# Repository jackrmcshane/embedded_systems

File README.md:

## Light Sensor System for the Hoosier National Forest

> This repository houses the code, circuit schematics, and 3D models for the light sensor system.

> The light sensor system is an autonomous, ultra-low power embedded microcontroller system designed to take light-level readings from the night sky. Over the course of hte next year, it will be deployed in teh Hoosier National Forest to collect sensor readings for the Forest Service in their attempt to gain 'dark sky' status.

> The software utilized by the system is an interrupt driven program that utilized the system's Real-Time Clock (RTC) to generate regular interrupts at fifteen minute intervals. These intervals are generated between the times of 8:00pm and 8:00am, daily, over the course of the system's one year lifetime so that the sensor system is able to capture how low the light levels reach over the course of each night. These readings are then stored bythe software in the system's FLASH memory back for collection at the end of the device's lifetime.

> TGhe electrical system, responsible for powering the system's CPU and peripheral devices, maximizes its operational life cycle by switching between a high powered running mode used for taking readings and low power mode which conserves the state of the machine whilst still limiting the expense of power. Utilizing the modes of operation that we do, the maximum lifetime of the light sensor system has been estimated to be three years using the STMCube software, allowing confidence that the system can operate for a year without issue.

> As part of the overall system, a 3D printable, water-resistant enclosure has been designed to house the electrical components. An enclosure such as the one we designed is a necessary part of the larger system not only because it will shield the PCB and its components from external forces such as dirt and rain while it is out in the forest, but it will also protect wildlife from damaging the electrical system and vice versa. The enclosure has a securable lid for easy access to the PCB and a port on the bottom of the enclosure for access to a 3-pin connector for later collection of the data captured by the light sensor system.

> The system has been designed to be as low cost as possible such that it may be produced en masse for the Forest Service so that they might deploy the devices throughout the 200,000 acres of the forest and maximize their chances to collect the low-light level readings that they need.

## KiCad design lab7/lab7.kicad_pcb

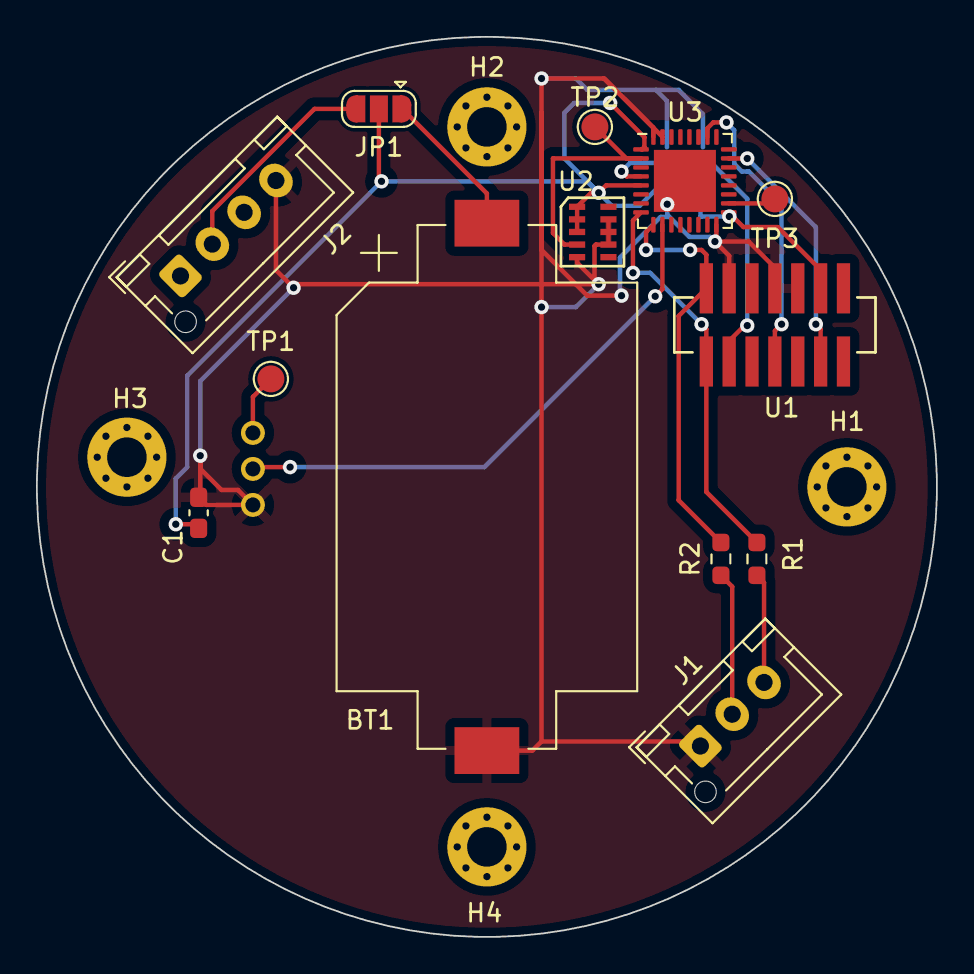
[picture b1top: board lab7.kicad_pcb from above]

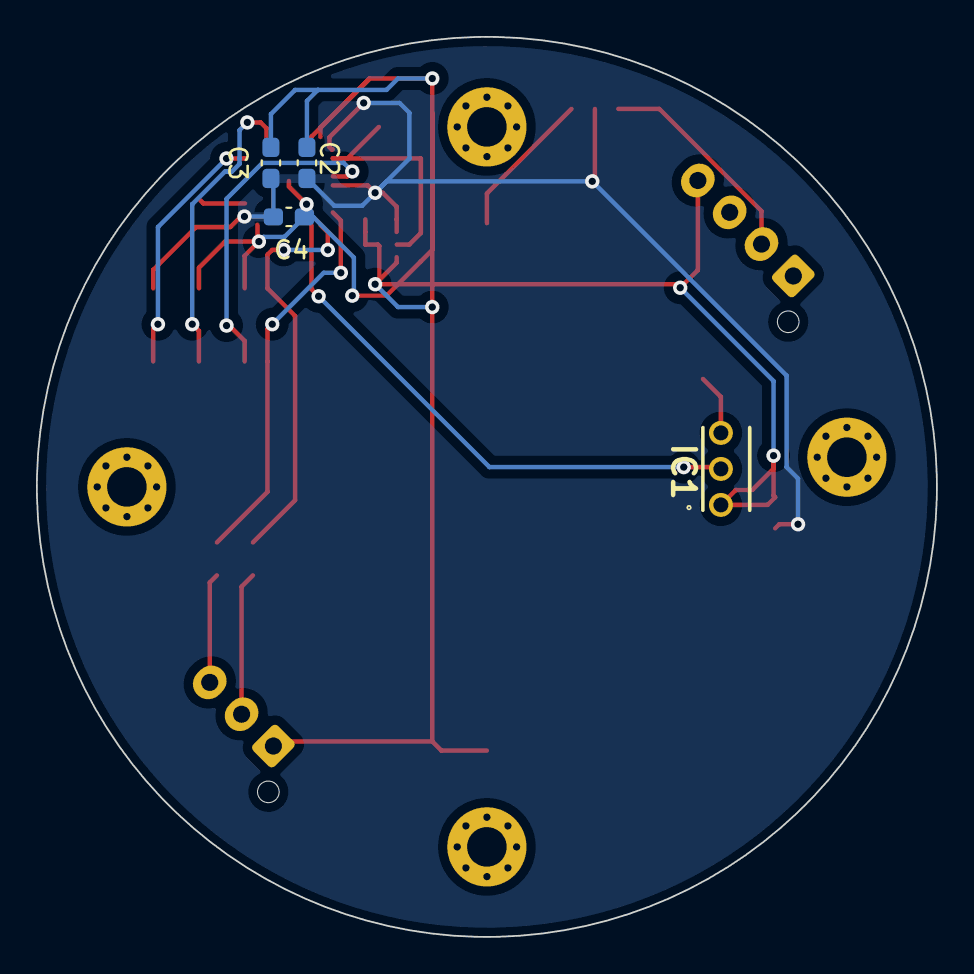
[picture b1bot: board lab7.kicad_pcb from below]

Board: 2 copper layers, 50.0 x 50.0 mm, 21 parts (4 on the bottom side), 15 nets.

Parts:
BT1: Battery_Cell; BatteryHolder_Keystone_1060_1x2032
C1, C3: 1uF; C_0603_1608Metric_Pad1.08x0.95mm_HandSolder
C2, C4: 0.1uF; C_0603_1608Metric_Pad1.08x0.95mm_HandSolder
H1, H2, H3, H4: MountingHole; MountingHole_2.2mm_M2_Pad_Via
IC1: TSL237S-LF
J1: Conn_01x03; JST_XH_B3B-XH-AM_1x03_P2.50mm_Vertical
J2: Conn_01x04; JST_XH_B4B-XH-AM_1x04_P2.50mm_Vertical
JP1: Jumper_3_Open; SolderJumper-3_P1.3mm_Open_RoundedPad1.0x1.5mm
R1, R2: R_US; R_0603_1608Metric_Pad0.98x0.95mm_HandSolder
TP1, TP2, TP3: TestPoint; TestPoint_Pad_D1.5mm
U1: STDC14; ftsh_14p_connector
U2: TG-3541CE
U3: STM32L432KCUx; QFN-32-1EP_5x5mm_P0.5mm_EP3.45x3.45mm

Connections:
/CLKOUT: TP3.1, U3.18 (PA8)
/NRST: U1.12 (NRST), U3.4 (NRST)
/RX: R2.2, U1.13 (VCP_RX), U3.9 (PA3)
/SWDIO: U1.4 (SWDIO), U3.23 (PA13)
/SWO: U1.8 (SWO), U3.26 (PB3)
/TX: R1.2, U1.14 (VCP_TX), U3.8 (PA2)
/oscillator: TP2.1, U2.4 (OUT), U3.2 (PC14)
/sensor_pwr: IC1.2 (VDD), U3.10 (PA4)
GND: BT1.2 (-), C1.2, C2.2, C3.2, C4.2, IC1.1 (GND), J1.1, J2.4, U1.5 (GND), U1.7 (GND), U1.11 (GNDDetect), U2.5 (GND), U2.7 (GND), U2.8 (GND), U2.9 (GND), U3.16 (VSS), U3.31 (PH3), U3.32 (VSS), U3.33 (VSS)
unnamed: BT1.1 (+), JP1.1 (A)
unnamed: IC1.3 (OUT), TP1.1
unnamed: J1.2, R2.1
unnamed: J1.3, R1.1
unnamed: J2.2, JP1.3 (B)
VDD: C1.1, C2.1, C3.1, C4.1, JP1.2 (C), U1.3 (T_VCC), U2.1 (OE), U2.2 (VCC), U2.3 (VCC), U3.1 (VDD), U3.5 (VDDA), U3.17 (VDD)

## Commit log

2022-05-12 end of semester
2022-05-14 added readme to repo
